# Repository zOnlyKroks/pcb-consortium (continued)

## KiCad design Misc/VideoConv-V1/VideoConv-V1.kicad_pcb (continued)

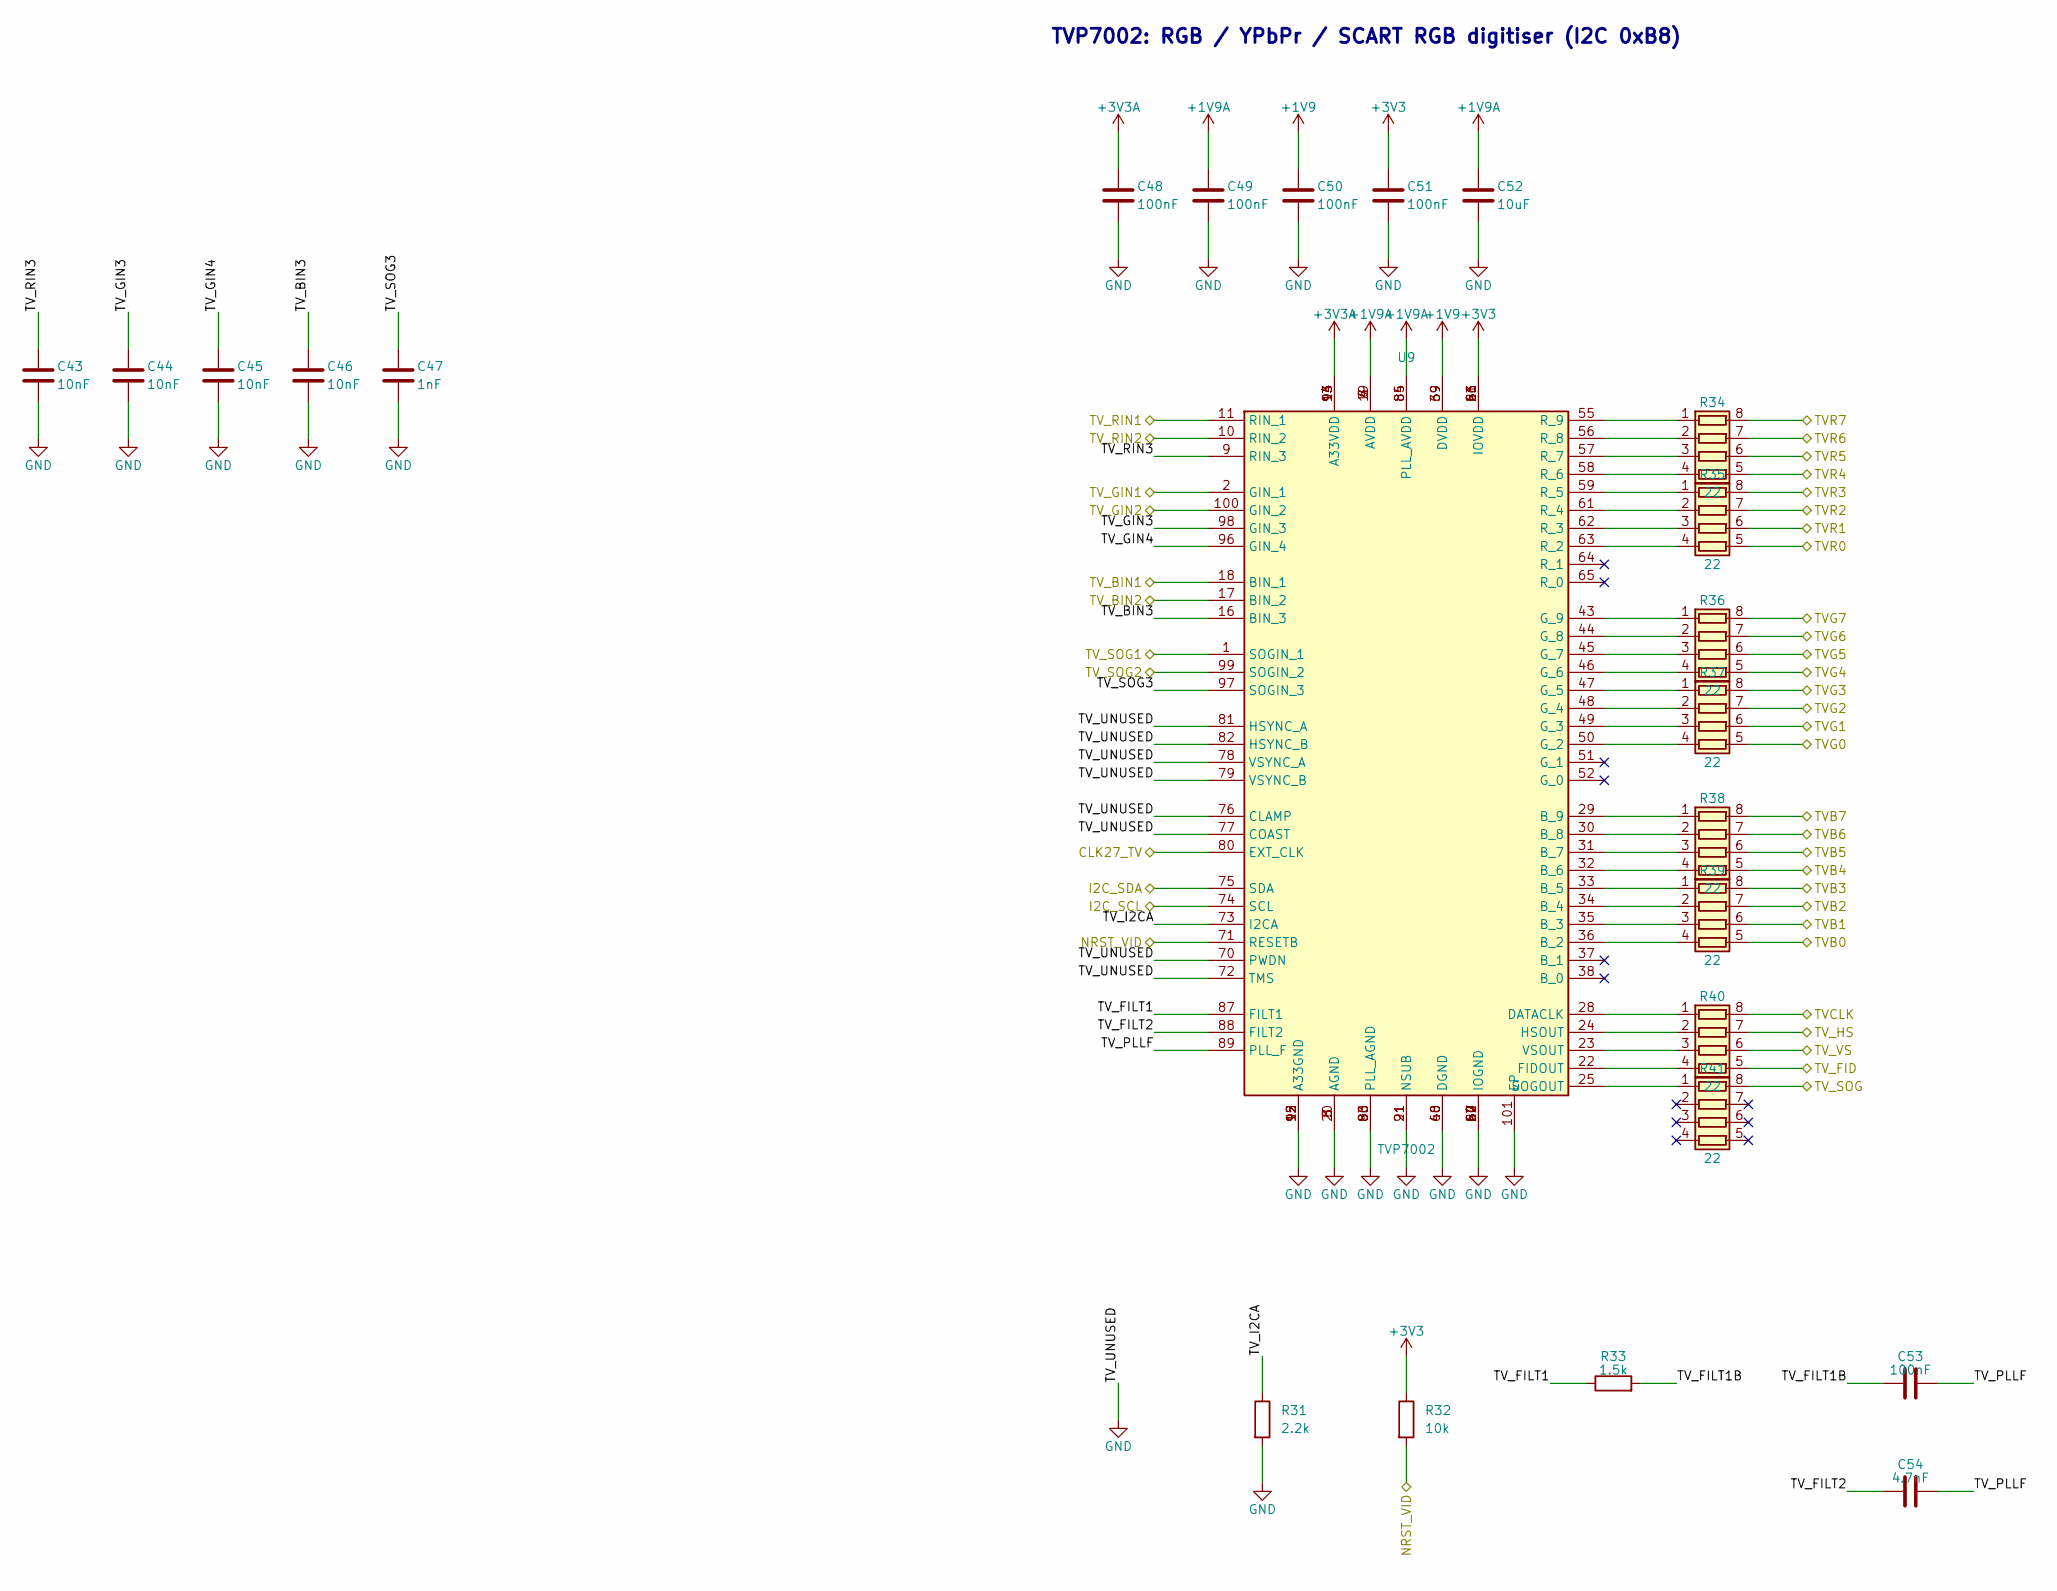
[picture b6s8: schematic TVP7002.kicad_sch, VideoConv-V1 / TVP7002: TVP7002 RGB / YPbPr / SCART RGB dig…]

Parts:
C43, C44, C45, C46: 10nF; C_0603_1608Metric; LCSC Part # C1589
C47: 1nF; C_0603_1608Metric; LCSC Part # C1588
C48, C49, C50, C51, C53: 100nF; C_0603_1608Metric; LCSC Part # C1591
C52: 10uF; C_0805_2012Metric; LCSC Part # C15850
C54: 4.7nF; C_0603_1608Metric; LCSC Part # C1621
R31: 2.2k; R_0603_1608Metric; LCSC Part # C4190
R32: 10k; R_0603_1608Metric; LCSC Part # C25804
R33: 1.5k; R_0603_1608Metric; LCSC Part # C22843
R34, R35, R36, R37, R38, R39, R40, R41: 22; R_Array_Convex_4x0603; LCSC Part # C12008
U9: TVP7002; TQFP-100-1EP_14x14mm_P0.5mm_EP5x5mm; MPN TVP7002PZP; LCSC Part # C3824085

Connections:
+1V9: C50.1, U9.39 (DVDD), U9.69 (DVDD); also elsewhere on the board
+1V9A: C49.1, C52.1, U9.4 (AVDD), U9.6 (AVDD), U9.7 (AVDD), U9.19 (AVDD), U9.84 (PLL_AVDD), U9.85 (PLL_AVDD); also elsewhere on the board
+3V3: C51.1, R32.1, U9.26 (IOVDD), U9.41 (IOVDD), U9.53 (IOVDD), U9.66 (IOVDD); also elsewhere on the board
+3V3A: C48.1, U9.13 (A33VDD), U9.14 (A33VDD), U9.93 (A33VDD), U9.94 (A33VDD); also elsewhere on the board
/CLK27_TV: U9.80 (EXT_CLK); also elsewhere on the board
/I2C_SCL: U9.74 (SCL); also elsewhere on the board
/I2C_SDA: U9.75 (SDA); also elsewhere on the board
/NRST_VID: R32.2, U9.71 (RESETB); also elsewhere on the board
/TVB0: R39.5 (R4.2); also elsewhere on the board
/TVB1: R39.6 (R3.2); also elsewhere on the board
/TVB2: R39.7 (R2.2); also elsewhere on the board
/TVB3: R39.8 (R1.2); also elsewhere on the board
/TVB4: R38.5 (R4.2); also elsewhere on the board
/TVB5: R38.6 (R3.2); also elsewhere on the board
/TVB6: R38.7 (R2.2); also elsewhere on the board
/TVB7: R38.8 (R1.2); also elsewhere on the board
/TVCLK: R40.8 (R1.2); also elsewhere on the board
/TVG0: R37.5 (R4.2); also elsewhere on the board
/TVG1: R37.6 (R3.2); also elsewhere on the board
/TVG2: R37.7 (R2.2); also elsewhere on the board
/TVG3: R37.8 (R1.2); also elsewhere on the board
/TVG4: R36.5 (R4.2); also elsewhere on the board
/TVG5: R36.6 (R3.2); also elsewhere on the board
/TVG6: R36.7 (R2.2); also elsewhere on the board
/TVG7: R36.8 (R1.2); also elsewhere on the board
/TVP7002/TV_BIN3: C46.1, U9.16 (BIN_3)
/TVP7002/TV_FILT1: R33.1, U9.87 (FILT1)
/TVP7002/TV_FILT1B: C53.1, R33.2
/TVP7002/TV_FILT2: C54.1, U9.88 (FILT2)
/TVP7002/TV_GIN3: C44.1, U9.98 (GIN_3)
/TVP7002/TV_GIN4: C45.1, U9.96 (GIN_4)
/TVP7002/TV_I2CA: R31.1, U9.73 (I2CA)
/TVP7002/TV_PLLF: C53.2, C54.2, U9.89 (PLL_F)
/TVP7002/TV_RIN3: C43.1, U9.9 (RIN_3)
/TVP7002/TV_SOG3: C47.1, U9.97 (SOGIN_3)
/TVR0: R35.5 (R4.2); also elsewhere on the board
/TVR1: R35.6 (R3.2); also elsewhere on the board
/TVR2: R35.7 (R2.2); also elsewhere on the board
/TVR3: R35.8 (R1.2); also elsewhere on the board
/TVR4: R34.5 (R4.2); also elsewhere on the board
/TVR5: R34.6 (R3.2); also elsewhere on the board
/TVR6: R34.7 (R2.2); also elsewhere on the board
/TVR7: R34.8 (R1.2); also elsewhere on the board
/TV_BIN1: U9.18 (BIN_1); also elsewhere on the board
/TV_BIN2: U9.17 (BIN_2); also elsewhere on the board
/TV_FID: R40.5 (R4.2); also elsewhere on the board
/TV_GIN1: U9.2 (GIN_1); also elsewhere on the board
/TV_GIN2: U9.100 (GIN_2); also elsewhere on the board
/TV_HS: R40.7 (R2.2); also elsewhere on the board
/TV_RIN1: U9.11 (RIN_1); also elsewhere on the board
/TV_RIN2: U9.10 (RIN_2); also elsewhere on the board
/TV_SOG: R41.8 (R1.2); also elsewhere on the board
/TV_SOG1: U9.1 (SOGIN_1); also elsewhere on the board
/TV_SOG2: U9.99 (SOGIN_2); also elsewhere on the board
/TV_VS: R40.6 (R3.2); also elsewhere on the board
GND: C43.2, C44.2, C45.2, C46.2, C47.2, C48.2, C49.2, C50.2, C51.2, C52.2, R31.2, U9.3 (AGND), U9.5 (AGND), U9.8 (AGND), U9.12 (A33GND), U9.15 (A33GND), U9.20 (AGND), U9.21 (NSUB), U9.27 (IOGND), U9.40 (DGND), U9.42 (IOGND), U9.54 (IOGND), U9.60 (IOGND), U9.67 (IOGND), U9.68 (DGND), U9.70 (PWDN), U9.72 (TMS), U9.76 (CLAMP), U9.77 (COAST), U9.78 (VSYNC_A), U9.79 (VSYNC_B), U9.81 (HSYNC_A), U9.82 (HSYNC_B), U9.83 (PLL_AGND), U9.86 (PLL_AGND), U9.90 (PLL_AGND), U9.91 (NSUB), U9.92 (A33GND), U9.95 (A33GND), U9.101 (EP); also elsewhere on the board
unnamed: R34.1 (R1.1), U9.55 (R_9)
unnamed: R34.2 (R2.1), U9.56 (R_8)
unnamed: R34.3 (R3.1), U9.57 (R_7)
unnamed: R34.4 (R4.1), U9.58 (R_6)
unnamed: R35.1 (R1.1), U9.59 (R_5)
unnamed: R35.2 (R2.1), U9.61 (R_4)
unnamed: R35.3 (R3.1), U9.62 (R_3)
unnamed: R35.4 (R4.1), U9.63 (R_2)
unnamed: R36.1 (R1.1), U9.43 (G_9)
unnamed: R36.2 (R2.1), U9.44 (G_8)
unnamed: R36.3 (R3.1), U9.45 (G_7)
unnamed: R36.4 (R4.1), U9.46 (G_6)
unnamed: R37.1 (R1.1), U9.47 (G_5)
unnamed: R37.2 (R2.1), U9.48 (G_4)
unnamed: R37.3 (R3.1), U9.49 (G_3)
unnamed: R37.4 (R4.1), U9.50 (G_2)
unnamed: R38.1 (R1.1), U9.29 (B_9)
unnamed: R38.2 (R2.1), U9.30 (B_8)
unnamed: R38.3 (R3.1), U9.31 (B_7)
unnamed: R38.4 (R4.1), U9.32 (B_6)
unnamed: R39.1 (R1.1), U9.33 (B_5)
unnamed: R39.2 (R2.1), U9.34 (B_4)
unnamed: R39.3 (R3.1), U9.35 (B_3)
unnamed: R39.4 (R4.1), U9.36 (B_2)
unnamed: R40.1 (R1.1), U9.28 (DATACLK)
unnamed: R40.2 (R2.1), U9.24 (HSOUT)
unnamed: R40.3 (R3.1), U9.23 (VSOUT)
unnamed: R40.4 (R4.1), U9.22 (FIDOUT)
unnamed: R41.1 (R1.1), U9.25 (SOGOUT)

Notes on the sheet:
TVP7002: RGB / YPbPr / SCART RGB digitiser (I2C 0xB8)

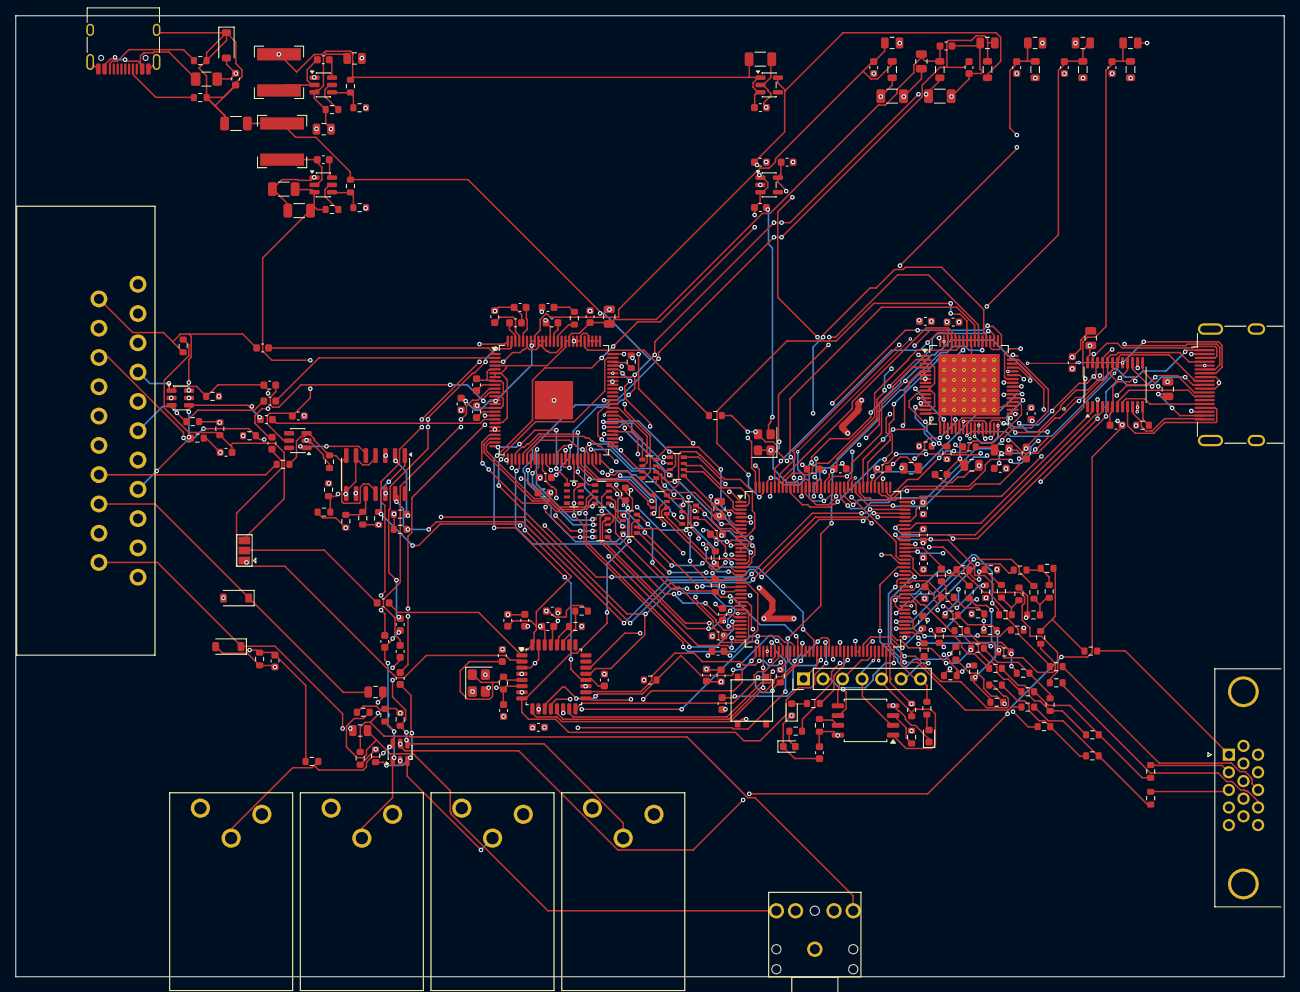
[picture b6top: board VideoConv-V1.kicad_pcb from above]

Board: 4 copper layers, 165.0 x 125.0 mm, 236 parts (0 on the bottom side), 250 nets.

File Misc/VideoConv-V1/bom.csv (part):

Reference,Value,Footprint,LCSC,MPN,Note,Symbol
C1,10uF,Capacitor_SMD:C_0805_2012Metric,C15850,,,Device:C
C2,10uF,Capacitor_SMD:C_0805_2012Metric,C15850,,,Device:C
C3,100nF,Capacitor_SMD:C_0603_1608Metric,C1591,,,Device:C
C4,100nF,Capacitor_SMD:C_0603_1608Metric,C1591,,,Device:C
C5,22uF,Capacitor_SMD:C_1206_3216Metric,C12891,,,Device:C
C6,22uF,Capacitor_SMD:C_1206_3216Metric,C12891,,,Device:C
C7,22uF,Capacitor_SMD:C_1206_3216Metric,C12891,,,Device:C
C8,22uF,Capacitor_SMD:C_1206_3216Metric,C12891,,,Device:C
C9,22uF,Capacitor_SMD:C_1206_3216Metric,C12891,,,Device:C
C10,22uF,Capacitor_SMD:C_1206_3216Metric,C12891,,,Device:C
C11,100nF,Capacitor_SMD:C_0603_1608Metric,C1591,,,Device:C
C12,1uF,Capacitor_SMD:C_0603_1608Metric,C29936,,,Device:C
C13,1uF,Capacitor_SMD:C_0603_1608Metric,C29936,,,Device:C
C14,2.2uF,Capacitor_SMD:C_0603_1608Metric,C23630,,,Device:C
C15,2.2uF,Capacitor_SMD:C_0603_1608Metric,C23630,,,Device:C
C16,10uF,Capacitor_SMD:C_0805_2012Metric,C15850,,,Device:C
C17,10uF,Capacitor_SMD:C_0805_2012Metric,C15850,,,Device:C
C18,10uF,Capacitor_SMD:C_0805_2012Metric,C15850,,,Device:C
C19,4.7uF,Capacitor_SMD:C_0805_2012Metric,C1746,,,Device:C
C20,10uF,Capacitor_SMD:C_0805_2012Metric,C15850,,,Device:C
C21,10uF,Capacitor_SMD:C_0805_2012Metric,C15850,,,Device:C
C22,100nF,Capacitor_SMD:C_0603_1608Metric,C1591,,,Device:C
C23,100nF,Capacitor_SMD:C_0603_1608Metric,C1591,,,Device:C
C24,100nF,Capacitor_SMD:C_0603_1608Metric,C1591,,,Device:C
C25,100nF,Capacitor_SMD:C_0603_1608Metric,C1591,,,Device:C
C26,100nF,Capacitor_SMD:C_0603_1608Metric,C1591,,,Device:C
C27,100nF,Capacitor_SMD:C_0603_1608Metric,C1591,,,Device:C
C28,4.7uF,Capacitor_SMD:C_0805_2012Metric,C1746,,"film or X7R, DC block",Device:C
C29,4.7uF,Capacitor_SMD:C_0805_2012Metric,C1746,,"film or X7R, DC block",Device:C
C30,100nF,Capacitor_SMD:C_0603_1608Metric,C1591,,,Device:C
C31,100nF,Capacitor_SMD:C_0603_1608Metric,C1591,,,Device:C
C32,100nF,Capacitor_SMD:C_0603_1608Metric,C1591,,,Device:C
C33,100nF,Capacitor_SMD:C_0603_1608Metric,C1591,,,Device:C
C34,100nF,Capacitor_SMD:C_0603_1608Metric,C1591,,,Device:C
C35,100nF,Capacitor_SMD:C_0603_1608Metric,C1591,,,Device:C
C36,1nF,Capacitor_SMD:C_0603_1608Metric,C1588,,"sync-on-green coupling, 1 nF per TVP7002 datasheet",Device:C
C37,1nF,Capacitor_SMD:C_0603_1608Metric,C1588,,"sync-on-green coupling, 1 nF per TVP7002 datasheet",Device:C
C38,820pF,Capacitor_SMD:C_0603_1608Metric,C307512,,"anti-alias, NP0",Device:C
C39,820pF,Capacitor_SMD:C_0603_1608Metric,C307512,,"anti-alias, NP0",Device:C
C40,100nF,Capacitor_SMD:C_0603_1608Metric,C1591,,,Device:C
C41,100nF,Capacitor_SMD:C_0603_1608Metric,C1591,,S-Video chroma from SCART pin 15,Device:C
C42,100nF,Capacitor_SMD:C_0603_1608Metric,C1591,,,Device:C
C43,10nF,Capacitor_SMD:C_0603_1608Metric,C1589,,,Device:C
C44,10nF,Capacitor_SMD:C_0603_1608Metric,C1589,,,Device:C
C45,10nF,Capacitor_SMD:C_0603_1608Metric,C1589,,,Device:C
C46,10nF,Capacitor_SMD:C_0603_1608Metric,C1589,,,Device:C
C47,1nF,Capacitor_SMD:C_0603_1608Metric,C1588,,,Device:C
C48,100nF,Capacitor_SMD:C_0603_1608Metric,C1591,,,Device:C
C49,100nF,Capacitor_SMD:C_0603_1608Metric,C1591,,,Device:C
C50,100nF,Capacitor_SMD:C_0603_1608Metric,C1591,,,Device:C
C51,100nF,Capacitor_SMD:C_0603_1608Metric,C1591,,,Device:C
C52,10uF,Capacitor_SMD:C_0805_2012Metric,C15850,,,Device:C
C53,100nF,Capacitor_SMD:C_0603_1608Metric,C1591,,,Device:C
C54,4.7nF,Capacitor_SMD:C_0603_1608Metric,C1621,,,Device:C
C55,27pF,Capacitor_SMD:C_0603_1608Metric,C1656,,,Device:C
C56,27pF,Capacitor_SMD:C_0603_1608Metric,C1656,,,Device:C
C57,1uF,Capacitor_SMD:C_0603_1608Metric,C29936,,,Device:C
C58,1uF,Capacitor_SMD:C_0603_1608Metric,C29936,,,Device:C
C59,1uF,Capacitor_SMD:C_0603_1608Metric,C29936,,,Device:C
C60,100nF,Capacitor_SMD:C_0603_1608Metric,C1591,,,Device:C
C61,100nF,Capacitor_SMD:C_0603_1608Metric,C1591,,,Device:C
C62,100nF,Capacitor_SMD:C_0603_1608Metric,C1591,,,Device:C
C63,100nF,Capacitor_SMD:C_0603_1608Metric,C1591,,,Device:C
C64,100nF,Capacitor_SMD:C_0603_1608Metric,C1591,,,Device:C
C65,100nF,Capacitor_SMD:C_0603_1608Metric,C1591,,,Device:C
C66,100nF,Capacitor_SMD:C_0603_1608Metric,C1591,,,Device:C
C67,100nF,Capacitor_SMD:C_0603_1608Metric,C1591,,,Device:C
C68,100nF,Capacitor_SMD:C_0603_1608Metric,C1591,,,Device:C
C69,100nF,Capacitor_SMD:C_0603_1608Metric,C1591,,,Device:C
C70,100nF,Capacitor_SMD:C_0603_1608Metric,C1591,,,Device:C
C71,100nF,Capacitor_SMD:C_0603_1608Metric,C1591,,,Device:C
C72,100nF,Capacitor_SMD:C_0603_1608Metric,C1591,,,Device:C
C73,100nF,Capacitor_SMD:C_0603_1608Metric,C1591,,,Device:C
C74,100nF,Capacitor_SMD:C_0603_1608Metric,C1591,,,Device:C
C75,100nF,Capacitor_SMD:C_0603_1608Metric,C1591,,,Device:C
C76,10uF,Capacitor_SMD:C_0805_2012Metric,C15850,,,Device:C
C77,10nF,Capacitor_SMD:C_0603_1608Metric,C1589,,,Device:C
C78,10uF,Capacitor_SMD:C_0805_2012Metric,C15850,,,Device:C
C79,100nF,Capacitor_SMD:C_0603_1608Metric,C1591,,,Device:C
C80,10uF,Capacitor_SMD:C_0805_2012Metric,C15850,,,Device:C
C81,100nF,Capacitor_SMD:C_0603_1608Metric,C1591,,,Device:C
C82,10uF,Capacitor_SMD:C_0805_2012Metric,C15850,,,Device:C
C83,100nF,Capacitor_SMD:C_0603_1608Metric,C1591,,,Device:C
C84,100nF,Capacitor_SMD:C_0603_1608Metric,C1591,,,Device:C
C85,10uF,Capacitor_SMD:C_0805_2012Metric,C15850,,,Device:C
C86,100nF,Capacitor_SMD:C_0603_1608Metric,C1591,,,Device:C
C87,100nF,Capacitor_SMD:C_0603_1608Metric,C1591,,,Device:C
C88,1uF,Capacitor_SMD:C_0805_2012Metric,C116352,,,Device:C
C89,100nF,Capacitor_SMD:C_0603_1608Metric,C1591,,,Device:C
C90,100nF,Capacitor_SMD:C_0603_1608Metric,C1591,,,Device:C
D1,SMF5.0A,Diode_SMD:D_SOD-123,C193402,,,Device:D_TVS
D2,SMF5.0CA,Diode_SMD:D_SOD-123,C364279,,bidirectional: line-level audio swings both ways,Device:D_TVS
D3,SMF5.0CA,Diode_SMD:D_SOD-123,C364279,,bidirectional: line-level audio swings both ways,Device:D_TVS
F1,1.5A PTC,Fuse:Fuse_1206_3216Metric,C49318384,"hold 1.5 A, 6 V",,Device:Polyfuse
FB1,600R@100MHz,Inductor_SMD:L_0805_2012Metric,C85837,,,Device:FerriteBead
FB2,600R@100MHz,Inductor_SMD:L_0805_2012Metric,C85837,,,Device:FerriteBead
FB3,600R@100MHz,Inductor_SMD:L_0805_2012Metric,C85837,,,Device:FerriteBead
FB4,600R@100MHz,Inductor_SMD:L_0805_2012Metric,C85837,,,Device:FerriteBead
FB5,600R@100MHz,Inductor_SMD:L_0805_2012Metric,C85837,,,Device:FerriteBead
FB6,600R@100MHz,Inductor_SMD:L_0805_2012Metric,C85837,,,Device:FerriteBead
J1,USB-C 5 V in,Connector_USB:USB_C_Receptacle_HRO_TYPE-C-31-M-12,C165948,,,Connector:USB_C_Receptacle_USB2.0_16P
J2,CVBS,VideoConv-V1:RCA_XDJK-0271-1650,C7527522,,"RCA jack, footprint to be chosen (not in KiCad stock)",Connector:Conn_Coaxial
J3,Y,VideoConv-V1:RCA_XDJK-0271-1650,C7527522,,"RCA jack, footprint to be chosen (not in KiCad stock)",Connector:Conn_Coaxial
J4,Pb,VideoConv-V1:RCA_XDJK-0271-1650,C7527522,,"RCA jack, footprint to be chosen (not in KiCad stock)",Connector:Conn_Coaxial
J5,Pr,VideoConv-V1:RCA_XDJK-0271-1650,C7527522,,"RCA jack, footprint to be chosen (not in KiCad stock)",Connector:Conn_Coaxial
J6,SCART,VideoConv-V1:SCART_Kycon_K-SCART-021,,21-pin right-angle PCB SCART socket (Kycon K-SCART-021 type),"not on LCSC: eBay / Electrokit 41022977 / Console5; footprint = Kycon K-SCART-021 drawing, compare with the seller's drawing",Connector:SCART-F
J7,Line out,VideoConv-V1:Jack_3.5mm_PJ-307N5_Horizontal,C692542,PJ-307N5,"SCART audio pass-through (no HDMI audio in v1); T / R order by geometry analogy with CUI SJ1-3525N, check L / R with a plug",Connector_Audio:AudioJack3
J8,PROG,Connector_PinHeader_2.54mm:PinHeader_1x07_P2.54mm_Vertical,C2894930,,,Connector_Generic:Conn_01x07
J9,HDMI,Connector_Video:HDMI_A_Molex_208658-1001_Horizontal,C916313,,,Connector:HDMI_A
J10,VGA,Connector_Dsub:DSUB-15-HD_Socket_Horizontal_P2.29x1.90mm_EdgePinOffset3.03mm_Housed_MountingHolesOffset4.94mm,C5172168,,,Connector:DE15_Socket_HighDensity
JP1,CVBS source,Jumper:SolderJumper-3_P1.3mm_Open_Pad1.0x1.5mm,,,"A = RCA composite, B = SCART pin 20 (CVBS or S-Video Y)",Jumper:SolderJumper_3_Open
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
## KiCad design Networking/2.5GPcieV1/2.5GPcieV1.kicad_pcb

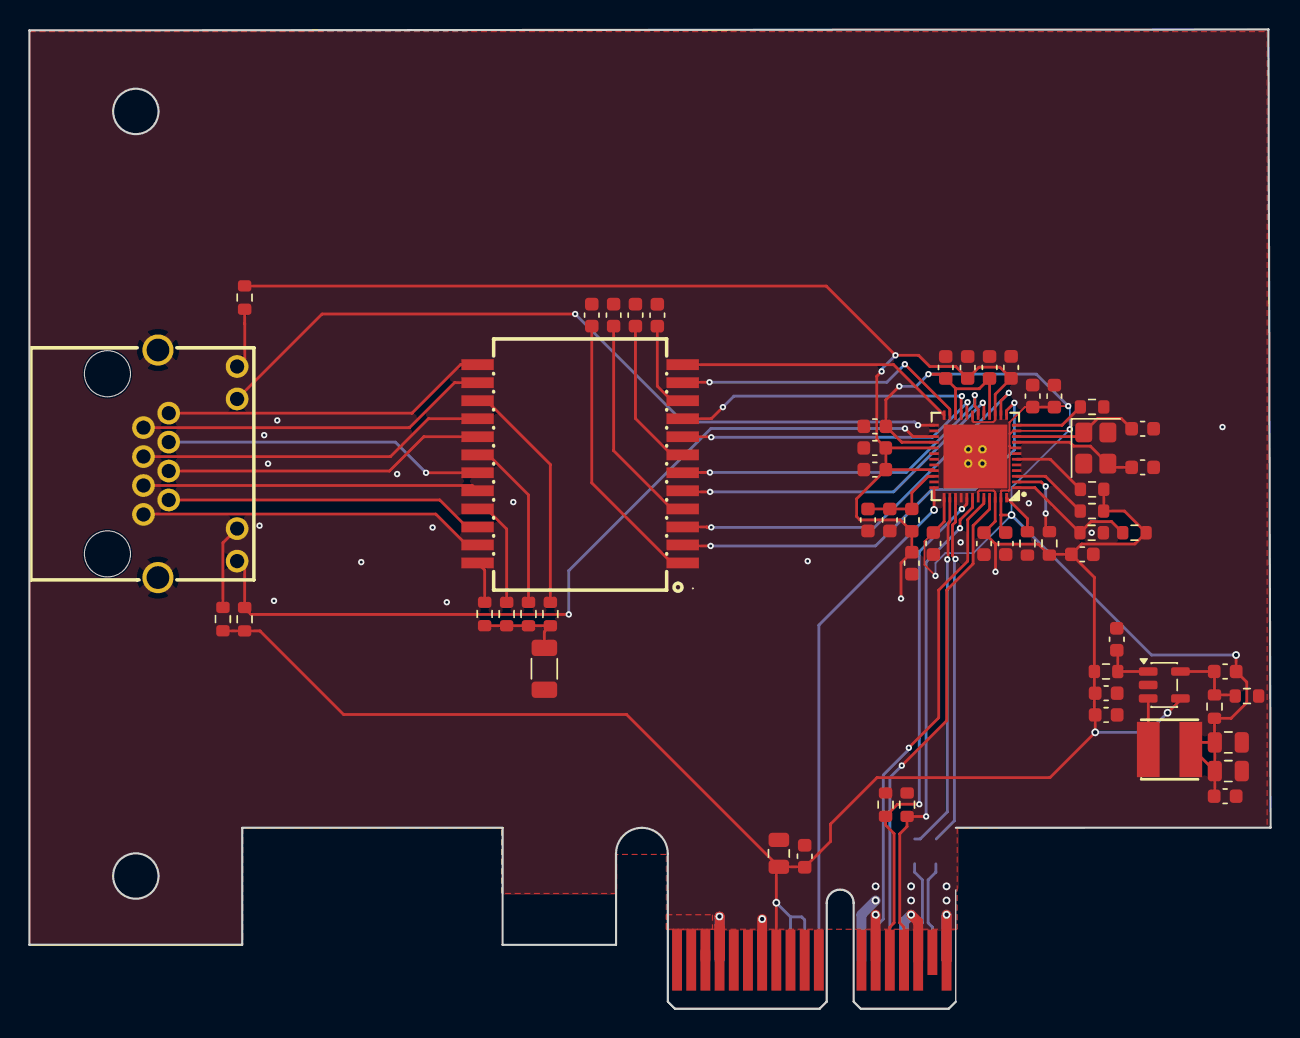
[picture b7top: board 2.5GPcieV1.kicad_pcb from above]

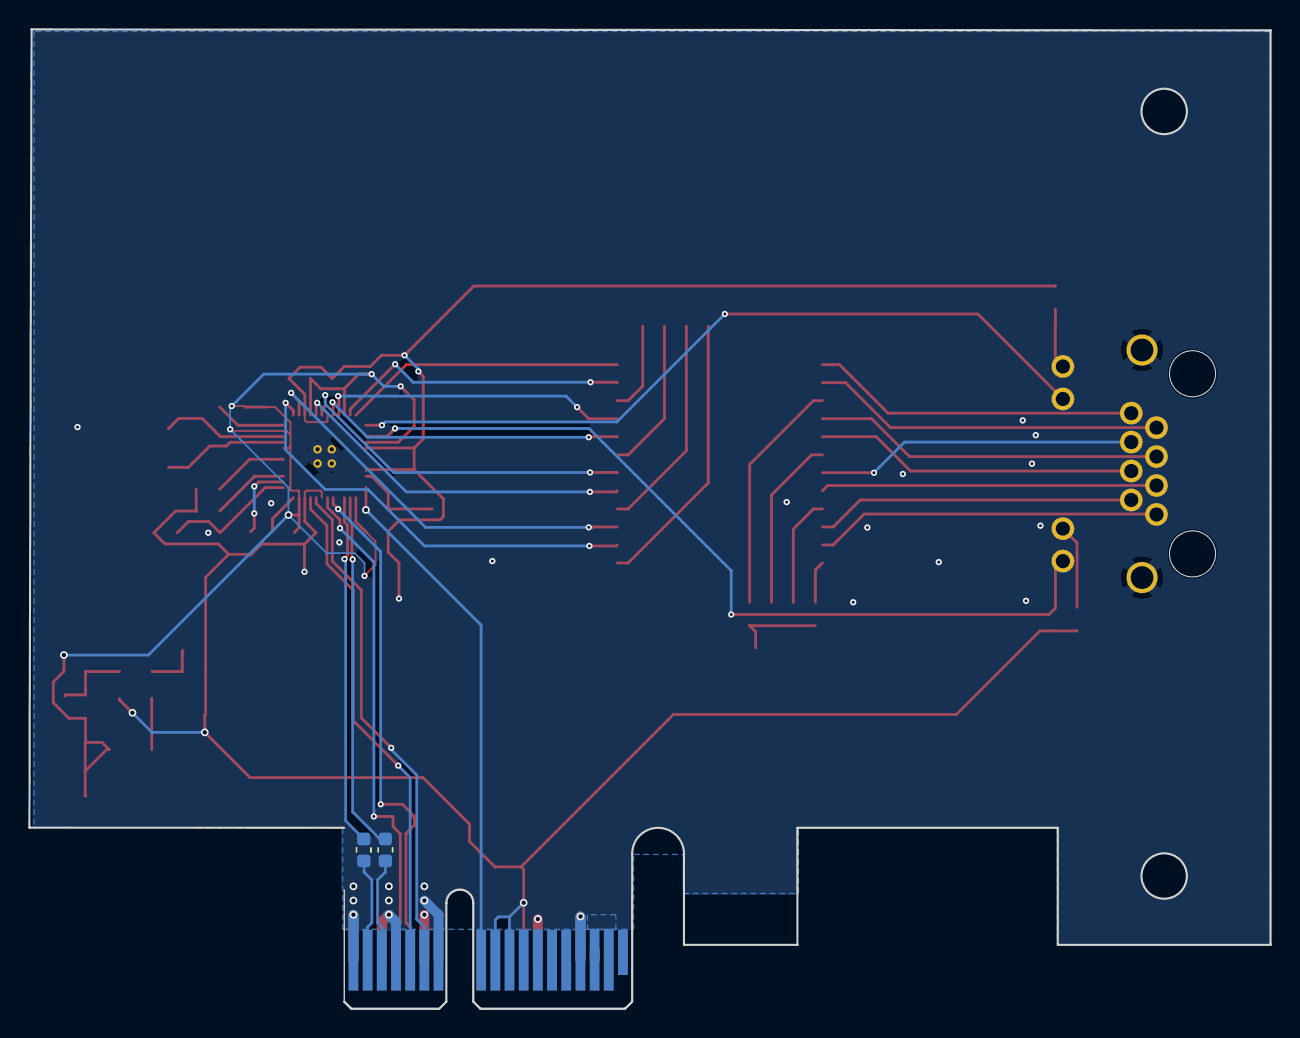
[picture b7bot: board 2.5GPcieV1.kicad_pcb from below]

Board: 4 copper layers, 87.5 x 69.1 mm, 61 parts (2 on the bottom side), 53 nets.

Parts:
C3, C9, C10: 22uF; C_0805_2012Metric
C4, C6, C7, C11, C12, C13, C14, C15, C16, C21, C23, C24, C25, C26, C27, C28, C29, C33, C34, C35, C36: 100nF; C_0603_1608Metric
C5, C17, C22, C30: 10uF; C_0603_1608Metric
C8: 22pF; C_0603_1608Metric
C18, C19: 100n; C_0603_1608Metric
C31, C32: 18pF; C_0603_1608Metric
C37: 1nF 2kV; C_1206_3216Metric
FB1: BLM18PG121SN1D; L_0603_1608Metric
J1: Bus_PCI_Express_x1; BUS_PCIexpress_x1
J2: RJ45-202-007-02; RJ45-TH_RJ45-202-007-02
L1: 2.2uH; IND-SMD_L4.0-W4.0_FNR40XXS
R1: 100k; R_0603_1608Metric
R2: 33k 1%; R_0603_1608Metric
R3: 56k 1%; R_0603_1608Metric
R4: 0R; R_0603_1608Metric
R5, R6, R7, R17: 4.7k; R_0603_1608Metric
R8: 1k; R_0603_1608Metric
R9: 15k; R_0603_1608Metric
R10: 2.49k 1%; R_0603_1608Metric
R11, R12, R13, R14: 75R; R_0603_1608Metric
R15, R16: 330R; R_0603_1608Metric
R20, R21: 49.9; R_0603_1608Metric
TR1: H2414QR; C4155001_XFMR-SMD_H2414QR
U1: RTL8125BG-CG; C3013605_TQFN-48_L6_0-W6_0-P0_40-BL-EP4_5
U2: SY8089A1AAC; SOT-23-5
Y1: 25MHz 12pF; Crystal_SMD_3225-4Pin_3.2x2.5mm

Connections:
+0V95: C8.1, C9.1, C10.1, C23.1, C24.1, C25.1, C26.1, C27.1, C28.1, C29.1, C30.1, L1.2, R2.1, U1.8 (DVDD09), U1.11 (AVDD09), U1.16 (AVDD09), U1.22 (AVDD09), U1.28 (DVDD09), U1.37 (EVDD09), U1.47 (DVDD09)
+3V3: C3.1, C4.1, C5.1, C6.1, C11.1, C12.1, C13.1, C14.1, C15.1, C16.1, C17.1, FB1.1, J1.A9 (+3.3V), J1.A10 (+3.3V), J1.B8 (+3.3V), R1.1, R5.1, R6.1, R7.1, R8.1, R15.2, R16.2, R17.2, U1.15 (AVDD33), U1.19 (AVDD33), U1.29 (DVDD33), U1.33 (AVDD33), U1.43 (EVDD33), U1.46 (DVDD33), U2.4 (IN)
/PCIe x1 + power/PCIexpress_connector/_PER0_N: C19.1, J1.A17 (PERn0)
/PCIe x1 + power/PCIexpress_connector/_PER0_P: C18.2, J1.A16 (PERp0)
/RTL8125BG + Ethernet/LED1: J2.12 (G-), R17.1, U1.27 (LED1/EESK)
/RTL8125BG + Ethernet/LED2: J2.10 (Y-), U1.25 (LED2/EEDO)
GND: C3.2, C4.2, C5.2, C6.2, C7.2, C9.2, C10.2, C11.2, C12.2, C13.2, C14.2, C15.2, C16.2, C17.2, C21.2, C22.2, C23.2, C24.2, C25.2, C26.2, C27.2, C28.2, C29.2, C30.2, C31.2, C32.2, C33.2, C34.2, C35.2, C36.2, C37.2, J1.A4 (GND), J1.A12 (GND), J1.A15 (GND), J1.A18 (GND), J1.B4 (GND), J1.B7 (GND), J1.B13 (GND), J1.B16 (GND), J1.B18 (GND), J2.13 (SHELL), R3.2, R4.1, R9.2, R10.2, R20.2, R21.2, U1.40 (GND), U1.49 (EP), U2.2 (GND), Y1.2 (G), Y1.4 (G)
unnamed: C37.1, R11.2, R12.2, R13.2, R14.2
unnamed: J2.11 (G+), R16.1
unnamed: J2.9 (Y+), R15.1
unnamed: R11.1, TR1.24 (MCT1)
unnamed: R12.1, TR1.21 (MCT2)
unnamed: R13.1, TR1.18 (MCT3)
unnamed: R14.1, TR1.15 (MCT4)
unnamed: J2.1, TR1.23 (MX1+)
unnamed: J2.2, TR1.22 (MX1-)
unnamed: J2.3, TR1.20 (MX2+)
unnamed: J2.6, TR1.19 (MX2-)
unnamed: J2.4, TR1.17 (MX3+)
unnamed: J2.5, TR1.16 (MX3-)
unnamed: J2.7, TR1.14 (MX4+)
unnamed: J2.8, TR1.13 (MX4-)
unnamed: C33.1, TR1.1 (TCT1)
unnamed: C34.1, TR1.4 (TCT2)
unnamed: C35.1, TR1.7 (TCT3)
unnamed: C36.1, TR1.10 (TCT4)
unnamed: TR1.2 (TD1+), U1.13 (MDIP0)
unnamed: TR1.3 (TD1-), U1.14 (MDIN0)
unnamed: TR1.5 (TD2+), U1.17 (MDIP1)
unnamed: TR1.6 (TD2-), U1.18 (MDIN1)
unnamed: TR1.8 (TD3+), U1.20 (MDIP2)
unnamed: TR1.9 (TD3-), U1.21 (MDIN2)
unnamed: TR1.11 (TD4+), U1.23 (MDIP3)
unnamed: TR1.12 (TD4-), U1.24 (MDIN3)
unnamed: C21.1, C22.1, FB1.2, U1.34 (AVDD33_XTAL)
unnamed: C31.1, U1.10 (CKXTAL1), Y1.1
unnamed: C32.1, U1.9 (CKXTAL2), Y1.3
unnamed: R6.2, U1.3 (GPI)
unnamed: R7.2, U1.6 (POW_EXT_SWR)
unnamed: R10.1, U1.12 (RSET)
unnamed: R4.2, U1.48 (~CLKREQB)
unnamed: R8.2, R9.1, U1.1 (~ISOLATEB)
unnamed: R5.2, U1.2 (~LANWAKEB)
unnamed: C7.1, R1.2, U2.1 (EN)
unnamed: C8.2, R2.2, R3.1, U2.5 (FB)
unnamed: L1.1, U2.3 (LX)
PCIE_RX_N: J1.B15 (PETn0), R20.1, U1.42 (HSIN)
PCIE_RX_P: J1.B14 (PETp0), R21.1, U1.41 (HSIP)
PCIE_TX_N: C19.2, U1.39 (HSON)
PCIE_TX_P: C18.1, U1.38 (HSOP)
PERST#: J1.A11 (~PERST), U1.36 (~PERSTB)
REFCLK_N: J1.A14 (REFCLK-), U1.45 (REFCLK_N)
REFCLK_P: J1.A13 (REFCLK+), U1.44 (REFCLK_P)
